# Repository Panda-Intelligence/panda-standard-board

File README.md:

# Current development entry — Panda Standard (E0.2 r26 / v0.1.1)

The current product is the **Panda Standard 4.7-inch parallel E0470A01-family single-board
engineering design**, with a replaceable 2050mAh LCO battery pack (`323576`) and a
finished-device maximum thickness of 7mm, including positive tolerances.
The exact pack identity, complete panel suffix/assembly and finished tolerance
stack remain unaccepted. A CAD candidate is **NOT FOR FABRICATION OR POWER**.

Start with [the current Single Unified PCB handoff](hardware/pico47/E02-R25-SINGLE-UNIFIED-PCB-20261029.md)
and [the Panda Standard source/build guide](hardware/pico47/README.md). Source code is
under `hardware/pico47/`; each finished single-board release (`Single.kicad_pcb` and its
native KiCad project/libraries) is committed under its version-named directory:
- [`hardware/pico47/v0.1.0/`](hardware/pico47/v0.1.0/) (`R25` full-rectangle 4-layer baseline)
- [`hardware/pico47/v0.1.1/`](hardware/pico47/v0.1.1/) (`R26` L-step 4-layer board with `X = 38.0 mm` battery bay clearance & Option 1 upper-right support bay)
Temporary generated rebuild reports and manufacturing archives remain in ignored `.work/`
or the external `panda-board-deliverables` directory.
The older Split-C1 / Product-D / Thin7 designs below are electrical donors or
historical experiments, not the current product or approval to export/order it.

Current r24 native checkpoint: **Core 16 opens; Display 0 opens; DRC errors,
warnings, parity and ERC are zero**. MUX0 is connected, while the remaining
non-ground routing is still unfinished. All 237 ground pads retain their reference
connections. **16 non-ground unconnected items remain; not for fabrication or
power.** The dated handoff records actual source replay, delivery archives and
engineering limits. Continue with
`capture_pico47_checkpoint.py --require-complete-ground`.

Run source regressions without EDA or manufacturing side effects:

```sh
python3 -m unittest discover -s hardware/pico47 -p 'test_*.py'
python3 -m unittest discover -s hardware/thin18-compact -p 'test_*.py'
```

Capture a continuation with `hardware/pico47/capture_pico47_checkpoint.py` only
after native review. It checks fresh DRC/ERC, exact rules/geometry/library
bindings and every previous native pad group. Missing evidence, lost connections
or increased opens/warnings reject the checkpoint. It never grants fabrication
or physical qualification, including when native counts happen to reach zero.

---

# Panda Standard Board

Open hardware design sources and engineering documentation for the **Panda Standard Board**, maintained by Panda Intelligence.

## Historical Split-C1 electrical donor

The historical electrical donor is the populated **Core-C1 96 x 68 mm / 4-layer** plus
**Display-C1 45 x 36 mm / 2-layer** design already split and routed on main.
Start with [Split-C1 handoff](hardware/thin18-compact/SPLIT-C1-HANDOFF.md) and the
[PG/PSEL functional migration](hardware/thin18-compact/SPLIT-C1-POWER-INTEGRITY.md).
Do not replace it with Thin7/portrait-R2 experimental CAD merely because an
experiment has a newer timestamp. Thin7 remains a separate, incomplete 7-mm
mechanical target and is not claimed by the Split-C1 bench prototype.

Inspect the historical pipeline without generating manufacturing data:

```sh
python3 hardware/thin18-compact/release_split_c1.py --target split-c1 --plan
```

Bare-board CAM/DFM, accepted PCBA supply and physical EVT are separate gates.
The new supervisor is a mainland part, but its exact assembly code/receipt is
not yet confirmed. No production qualification or actual purchase is implied.

## Historical published Thin18 baseline

The earlier published integrated-board engineering baseline was:

- **Board:** Thin18 domestic EVT
- **PCB checkpoint:** `routing142`
- **PCB SHA-256:** `ccc19c5402f633638ed72e7c94a92375684037a1f9c04f63072dc58f86c16071`
- **KiCad validation:** 0 DRC violations, 0 unconnected items, 0 schematic-parity errors; ERC 0
- **Status:** engineering / EVT — **not a manufacturing release**

The baseline includes the current right-side microSD access geometry. Manufacturing, assembly, SI/PI, RF, thermal, tolerance-stack and physical EVT qualification remain separate release gates.

## Repository layout

```text
hardware/
  thin18/
    routing142/        Current KiCad engineering baseline and machine-readable verification evidence
docs/
  design/              Electrical architecture, interfaces, power tree, constraints and design rules
  verification/        ERC/layout/fabrication-readiness engineering reviews
  mechanical/          Board/mechanical interface review notes
LICENSES/
```

## Opening the historical donor design

The design was validated with **KiCad 10.0.5**. Open the complete project under:

```text
hardware/thin18-compact/core-c1-96x68-split/eda/core/PANDA-STD-CORE-EVT/PANDA-THIN16/
hardware/thin18-compact/display-c1-45x36-production-bom/
```

Project-local symbol and footprint libraries are included where the design depends on them.

## Product visualization

Explore the [interactive Thin18 routing142 assembly model](hardware/thin18/routing142/visualization/Panda-thin18-routing142-exploded.html) or watch the [exploded-view video on YouTube](https://youtu.be/T_Nb8tvqas8).

The model is an engineering visualization for design communication. Mechanical fit and manufacturing readiness require separate validation.

## Verification boundary

A clean KiCad DRC/ERC result means the design database is internally consistent. It does **not** establish production qualification, regulatory compliance, component derating, RF performance, thermal margin, assembly yield or mechanical fit of real production parts.

Use tagged manufacturing releases, when available, for fabrication rather than assuming the newest engineering checkpoint is production-ready.

## Licensing

Hardware design sources: **CERN-OHL-S-2.0**.

Documentation: **CC BY-SA 4.0**, unless otherwise noted.

Third-party component models, symbols, footprints, manufacturer names and trademarks retain their respective rights and licensing terms.

## Split-C1 executable control follow-up

[Portable bench-control core](firmware/split_c1/README.md) implements tested
XL9535/SGM41513/SGM37601 sequencing and a read-only QMI8658A identity probe.
Host tests and native pin/address binding checks run in the explicit Split-C1
export pipeline. This is not product-firmware integration or physical EVT.
The [hardware-finish ECO](hardware/thin18-compact/SPLIT-C1-HARDWARE-FINISH.md) adds default-off charge authorization and a native GPIO2 shutdown path.
Read the updated control binding before using any older firmware. Physical EVT and accepted assembly supply remain separate gates.

## Current fabrication entry

The combined review package contains a generated `START-HERE.md`; use its
separate Core/Display Gerber paths and source hashes. The
[fabrication handoff](hardware/thin18-compact/JLC-PROTOTYPE-HANDOFF.md) now matches
the native four-layer35um Core copper construction and ENIG/green-mask selection.
C301 now has checked1.9mm round PTHs instead of short slots; the actual stackup
and assembly process still need CAM acceptance.
Native DRC/DFM success is not automatic fabrication/PCBA order approval.

## Split-C1 SMT process selection

The native [assembly-process auditor](hardware/thin18-compact/audit_split_c1_assembly_process.py)
and its tests now run before fabrication export. Core contains13 drilled vias
intersecting SMT copper lands; its order must explicitly include epoxy filling
and copper capping for the generated list. This is distinct from soldermask
tenting/plugging and must not fill component lead holes or slots. The generated
prototype package includes ASSEMBLY-PROCESS.md and per-board VIA-IN-PAD.csv,
bound to the saved PCB and checked against Excellon drill hits. Small WLCSP and
connector lands retain ENIG and need assembler stencil/process confirmation.
No source copper is changed by this audit; supplier acceptance is still required.

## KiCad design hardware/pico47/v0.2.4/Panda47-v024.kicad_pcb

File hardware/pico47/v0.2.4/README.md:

# Panda Standard 4.7 — main board v0.2.4 / E07

- **Board**: `Panda47-v024.kicad_pcb`. 4 layers, 0.8 mm. 63 × 48 mm with R4 bottom corners, the mid-mount USB-C notch
  and a speaker notch in the top-left corner, for a 67.0 × 133.7 × 7.3 mm device. See the
  [E07 note](../E07-V024-HAND-LAYOUT-SPEAKER-NOTCH-20261113.md).
- **Changes from v0.2.2**:
  - Charger, 3.3 V buck, front-light boost, RF, crystal and the VBUS / battery trunks are laid by hand
    (`../v024/design_v024.py`) and locked before autorouting. Power and HV tracks are widened after routing.
  - Cell protection moved into the pack: U907, R940, C940 and J301 are removed. J302 is a 3-pin header
    (B+ / B− / NTC) for a 3.0 × 57 × 79 mm pack with PCM and NTC.
  - Speaker notch; the audio amplifier and the speaker landing sit next to it.
  - New C817 (4.7 µF, same part as C804): VN reservoir right at the rectifier D802. New C818 (2.2 µF 0402, same
    part as C304): input capacitor at U810 pin 24. C816 dropped. C506 moved to the audio amplifier.
  - Test pads TP5 (FL_VOUT), TP6 (3V3_SD) and TPG2 (GND) added: 18 in total.
  - Connectors: the pack plugs into J302 (JST ACH 3-pin) and the antenna into J507 (MHF4); FL_PWM moved off the
    boot-strap pin (E07 note §8–9).
  - Board fixing: two soldered M1.6 nuts H2 / H3 at the top edge for screws from the back of the shell, two shell
    lips over the bottom edge, and two non-plated locating holes MH1 / MH2 for shell pins (E07 note §7 and §10).
  - Three fiducials. Net classes Power 0.3 mm, HV 0.2 mm, RF 0.17 mm.
- **Schematic**: `Panda47-v024.kicad_sch` (index) + 8 sheets, generated from the netlist. The netlist is identical to
  the board.
- **Libraries**: `Panda47v2.pretty` (the v0.2.2 set; the U901 pin-1 dot is moved). Symbols: `Panda7.kicad_sym`.
- **Native checks** (KiCad 10.0.7, in this directory): ERC 0. DRC 0 violations, 0 unconnected, 0 schematic parity
  (`--severity-all`).
- **Status**: `manufacturing_release = false`. Open items are listed in §6 of the E07 note; the main ones are a
  custom-pack quote for the cell (no datasheet exists for this size) and a speaker sample. 22 via-in-pad holes need
  resin fill and a plated cap. The order pack (153 placements, 72 BOM lines) is outside Git.

## Build path

Scripts are in `../v020/`, `../v023/` and `../v024/`; run them with `PANDA47_VARIANT=v024` and
`PANDA47_FP_DIR=hardware/pico47/v0.2.4/Panda47v2.pretty`. Freerouting is not deterministic, so this KiCad project,
not a replay, is the source of truth.

1. `make_netlist_v020.py` → netlist (174 parts including 18 test pads).
2. `v024/design_v024.py` (hand blocks → `hand.json`), `v024/make_anchors_v024.py`, `v020/place_v020.py`; run the
   three twice so the hand-copper keep-outs reach the placer. Result: `v024/layout/placement_v024.json`.
3. `build_v020_pcb.py`, `v023/precopper_v023.py` (locked hand copper), `gnd_stitch_v020.py`, Freerouting 60 passes.
4. Grid router (`router_v020.py` + `apply_router_v020.py`) with `v024/layout/spec_left.json`,
   `spec_touch_int.json` and `spec_d11.json`, with `eco_touch_int.py` and `eco_d11.py` in between (E07 note §4).
5. `finish_v020.py`, `prune_dangling_v020.py` / `trim_dangling_v020.py`, `v023/widen_v023.py`,
   `v023/fiducials_v023.py`, `silk_v020.py`, `info_silk_v02x.py` with `v024/v024_silk.json`, then
   `v024/layout/eco_final.py`.
6. `v024/layout/eco_vp.py`, `eco_pmic.py` (adds C817), the grid router with `spec_pmic.json`, prune / trim, widen
   and `silk_v020.py` again (E07 note §4 steps 9–10). The ECO scripts use `layout/ecolib.py`.
   Then `eco_cin.py` (C818, L802, C506) with `spec_cin.json`, `eco_tp.py` and `eco_tp_silk.py` (steps 11–12).
7. `build_v020_sch.py`, `sync_board_sch_v020.py`, `set_fields_v020.py`; `export_orderpack_v020.py` for the order pack.

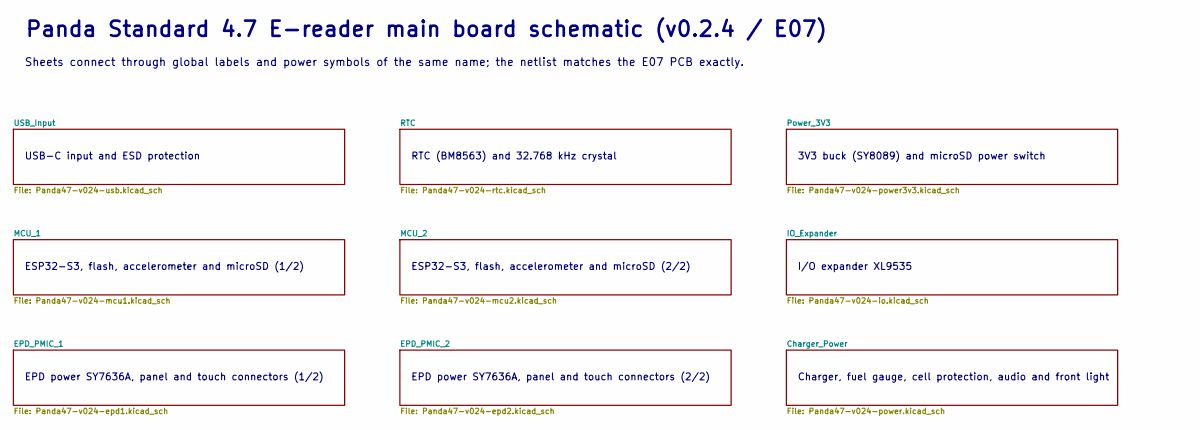
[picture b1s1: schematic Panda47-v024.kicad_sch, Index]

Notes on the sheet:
Panda Standard 4.7 E-reader main board schematic (v0.2.4 / E07)
Sheets connect through global labels and power symbols of the same name; the netlist matches the E07 PCB exactly.
USB-C input and ESD protection
RTC (BM8563) and 32.768 kHz crystal
3V3 buck (SY8089) and microSD power switch
ESP32-S3, flash, accelerometer and microSD (1/2)
ESP32-S3, flash, accelerometer and microSD (2/2)
I/O expander XL9535
EPD power SY7636A, panel and touch connectors (1/2)
EPD power SY7636A, panel and touch connectors (2/2)
Charger, fuel gauge, cell protection, audio and front light

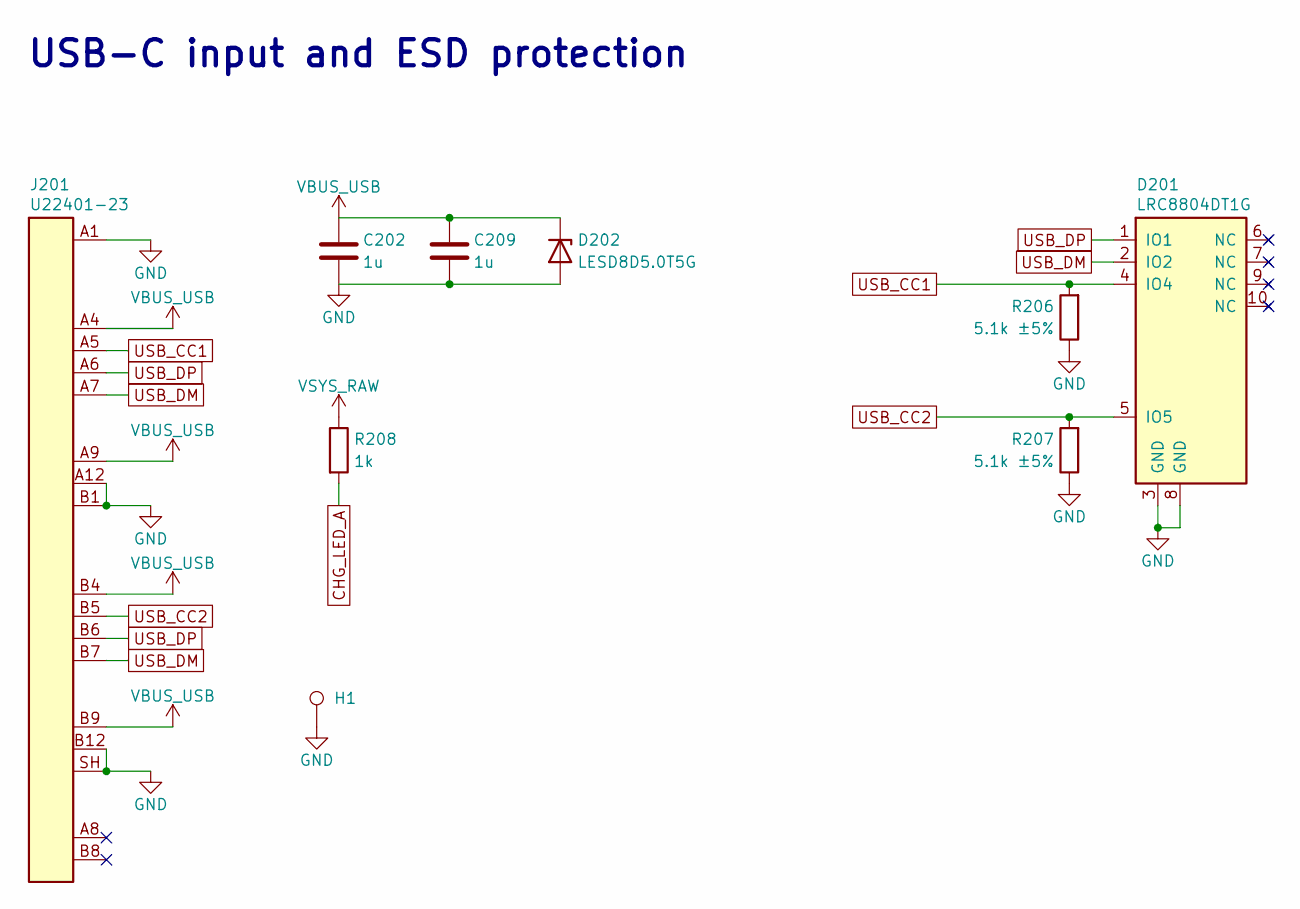
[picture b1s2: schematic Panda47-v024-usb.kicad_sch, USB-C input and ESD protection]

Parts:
C202: 1u / VBUS; C202_Core; MPN CL10A105KB8NNNC; LCSC C15849
C209: 1u; C209_Core; MPN CL10A105KB8NNNC; LCSC C15849
D201: LRC8804DT1G; D201_Core; MPN LRC8804DT1G; LCSC C2912064
D202: LESD8D5.0T5G; D202_Core; MPN LESD8D5.0T5G; LCSC C172414
H1: M1.6 SMT nut; SMTSO_M1.6_L1; MPN SMTSO1610MTJ; LCSC C2928167
J201: U22401-23 / MID-MOUNT; J201_Core; MPN U22401-23; LCSC C49325733
R206: 5.1k ±5% / USB-C Rd; R206_Core; MPN 0402WGF5101TCE; LCSC C25905
R207: 5.1k ±5% / USB-C Rd; R207_Core; MPN 0402WGF5101TCE; LCSC C25905
R208: 1k; R_0402_1005Metric; MPN 0402WGF1001TCE; LCSC C11702

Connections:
CHG_LED_A: R208.2; also elsewhere on the board
GND: C202.2, C209.2, D201.3 (GND), D201.8 (GND), D202.2 (A), H1.1, J201.A1 (A1_A1), J201.A12 (A12_A12), J201.B1 (B1_B1), J201.B12 (B12_B12), J201.SH (SH_SH), R206.1, R207.1; also elsewhere on the board
USB_CC1: D201.4 (IO4), J201.A5 (A5_A5), R206.2
USB_CC2: D201.5 (IO5), J201.B5 (B5_B5), R207.2
USB_DM: D201.2 (IO2), J201.A7 (A7_A7), J201.B7 (B7_B7); also elsewhere on the board
USB_DP: D201.1 (IO1), J201.A6 (A6_A6), J201.B6 (B6_B6); also elsewhere on the board
VBUS_USB: C202.1, C209.1, D202.1 (K), J201.A4 (A4_A4), J201.A9 (A9_A9), J201.B4 (B4_B4), J201.B9 (B9_B9); also elsewhere on the board
VSYS_RAW: R208.1; also elsewhere on the board

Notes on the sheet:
USB-C input and ESD protection

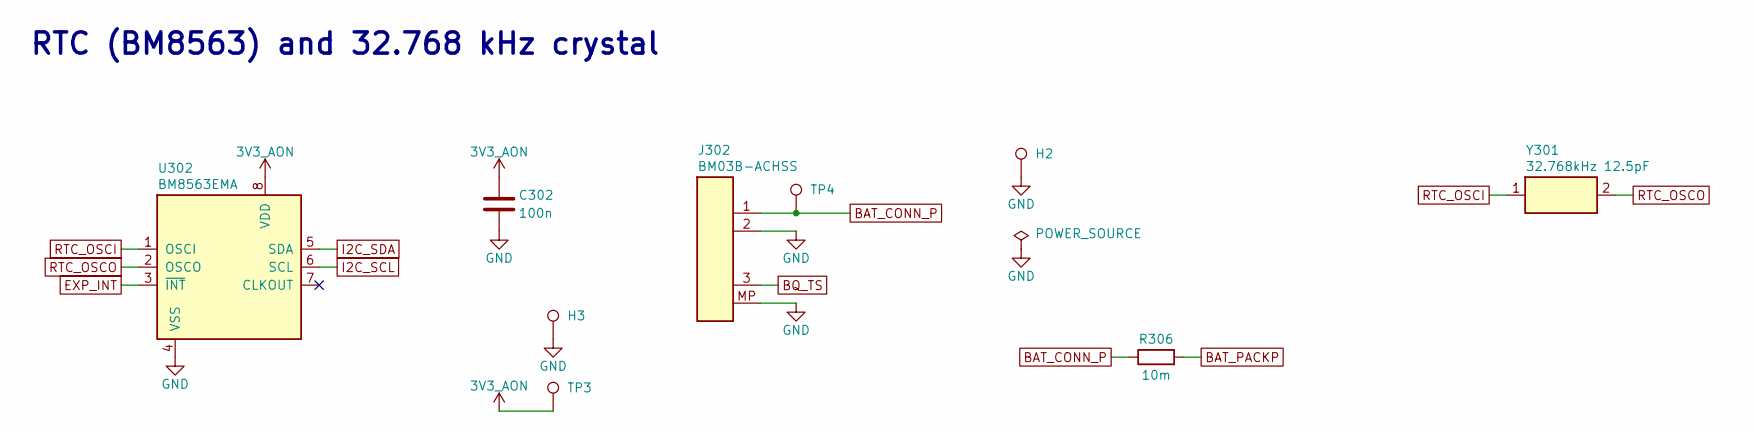
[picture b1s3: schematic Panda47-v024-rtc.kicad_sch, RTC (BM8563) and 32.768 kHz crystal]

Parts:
C302: 100n / RTC VDD; C302_Core; MPN CL05B104KB54PNC; LCSC C307331
H2, H3: M1.6 SMT nut; SMTSO_M1.6_L1; MPN SMTSO1620MTJ; LCSC C2916317
J302: BM03B-ACHSS / pack; JST_ACH_BM03B-ACHSS-GAN-ETF_1x03-1MP_P1.20mm_Vertical; MPN BM03B-ACHSS-GAN-ETF(LF)(SN); LCSC C5118705
R306: 10m / CW2217 SHUNT; R306_Core; MPN FRM121WFR010TM; LCSC C7467248
TP3: 3V3_AON; TP3_Core; MPN NOT_A_PURCHASED_PART
TP4: BAT+; TP4_Core; MPN NOT_A_PURCHASED_PART
U302: BM8563EMA; MSOP-8_3x3mm_P0.65mm; MPN BM8563EMA; LCSC C269878
Y301: 32.768kHz 12.5pF; Crystal_SMD_3215-2Pin_3.2x1.5mm; MPN X321532768KGD2SI; LCSC C620155

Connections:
3V3_AON: C302.1, TP3.1, U302.8 (VDD); also elsewhere on the board
BAT_CONN_P: J302.1, R306.1, TP4.1; also elsewhere on the board
BAT_PACKP: R306.2; also elsewhere on the board
BQ_TS: J302.3; also elsewhere on the board
EXP_INT: U302.3 (~INT); also elsewhere on the board
GND: C302.2, H2.1, H3.1, J302.2, J302.MP, U302.4 (VSS); also elsewhere on the board
I2C_SCL: U302.6 (SCL); also elsewhere on the board
I2C_SDA: U302.5 (SDA); also elsewhere on the board
RTC_OSCI: U302.1 (OSCI), Y301.1
RTC_OSCO: U302.2 (OSCO), Y301.2

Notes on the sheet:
RTC (BM8563) and 32.768 kHz crystal

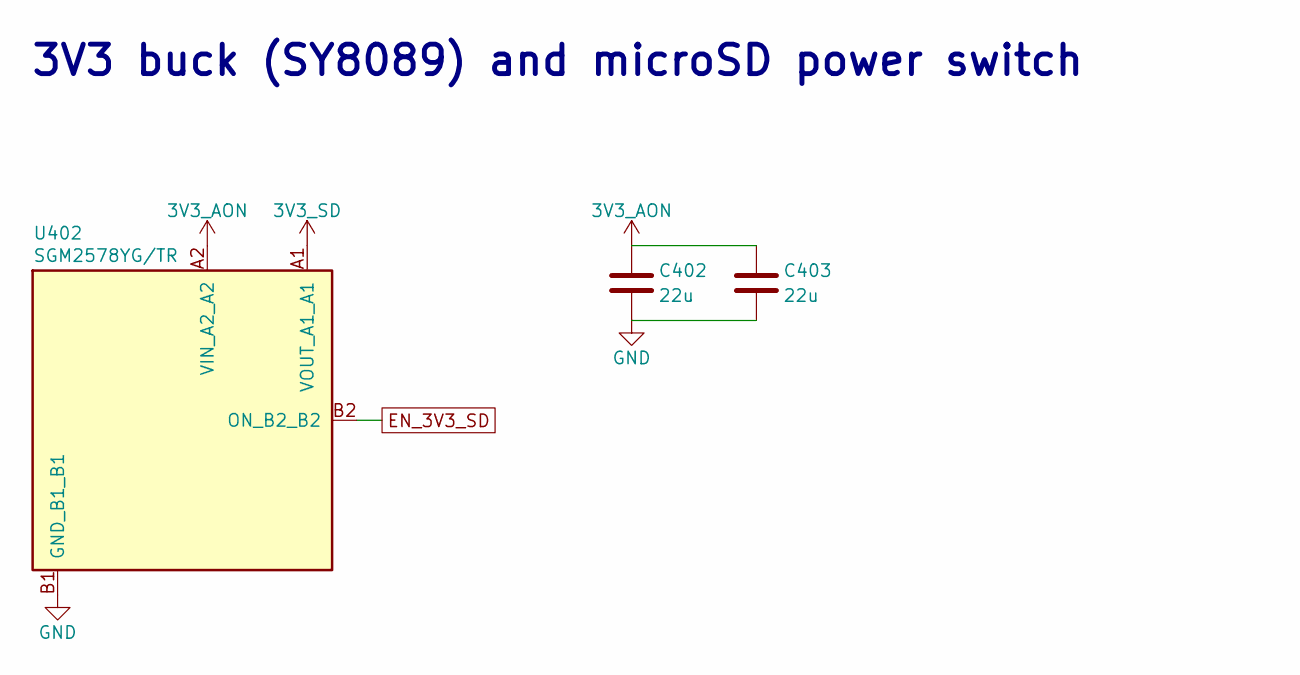
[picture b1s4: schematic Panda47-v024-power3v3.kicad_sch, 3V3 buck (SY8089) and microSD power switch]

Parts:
C402: 22u / VOUT; C402_Core; MPN TCC0603X5R226M100CT; LCSC C20416425
C403: 22u / VOUT; C403_Core; MPN TCC0603X5R226M100CT; LCSC C20416425
U402: SGM2578YG/TR; U402_Core; MPN SGM2578YG/TR; LCSC C403706

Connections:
3V3_AON: C402.1, C403.1, U402.A2 (VIN_A2_A2); also elsewhere on the board
3V3_SD: U402.A1 (VOUT_A1_A1); also elsewhere on the board
EN_3V3_SD: U402.B2 (ON_B2_B2); also elsewhere on the board
GND: C402.2, C403.2, U402.B1 (GND_B1_B1); also elsewhere on the board

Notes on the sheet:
3V3 buck (SY8089) and microSD power switch

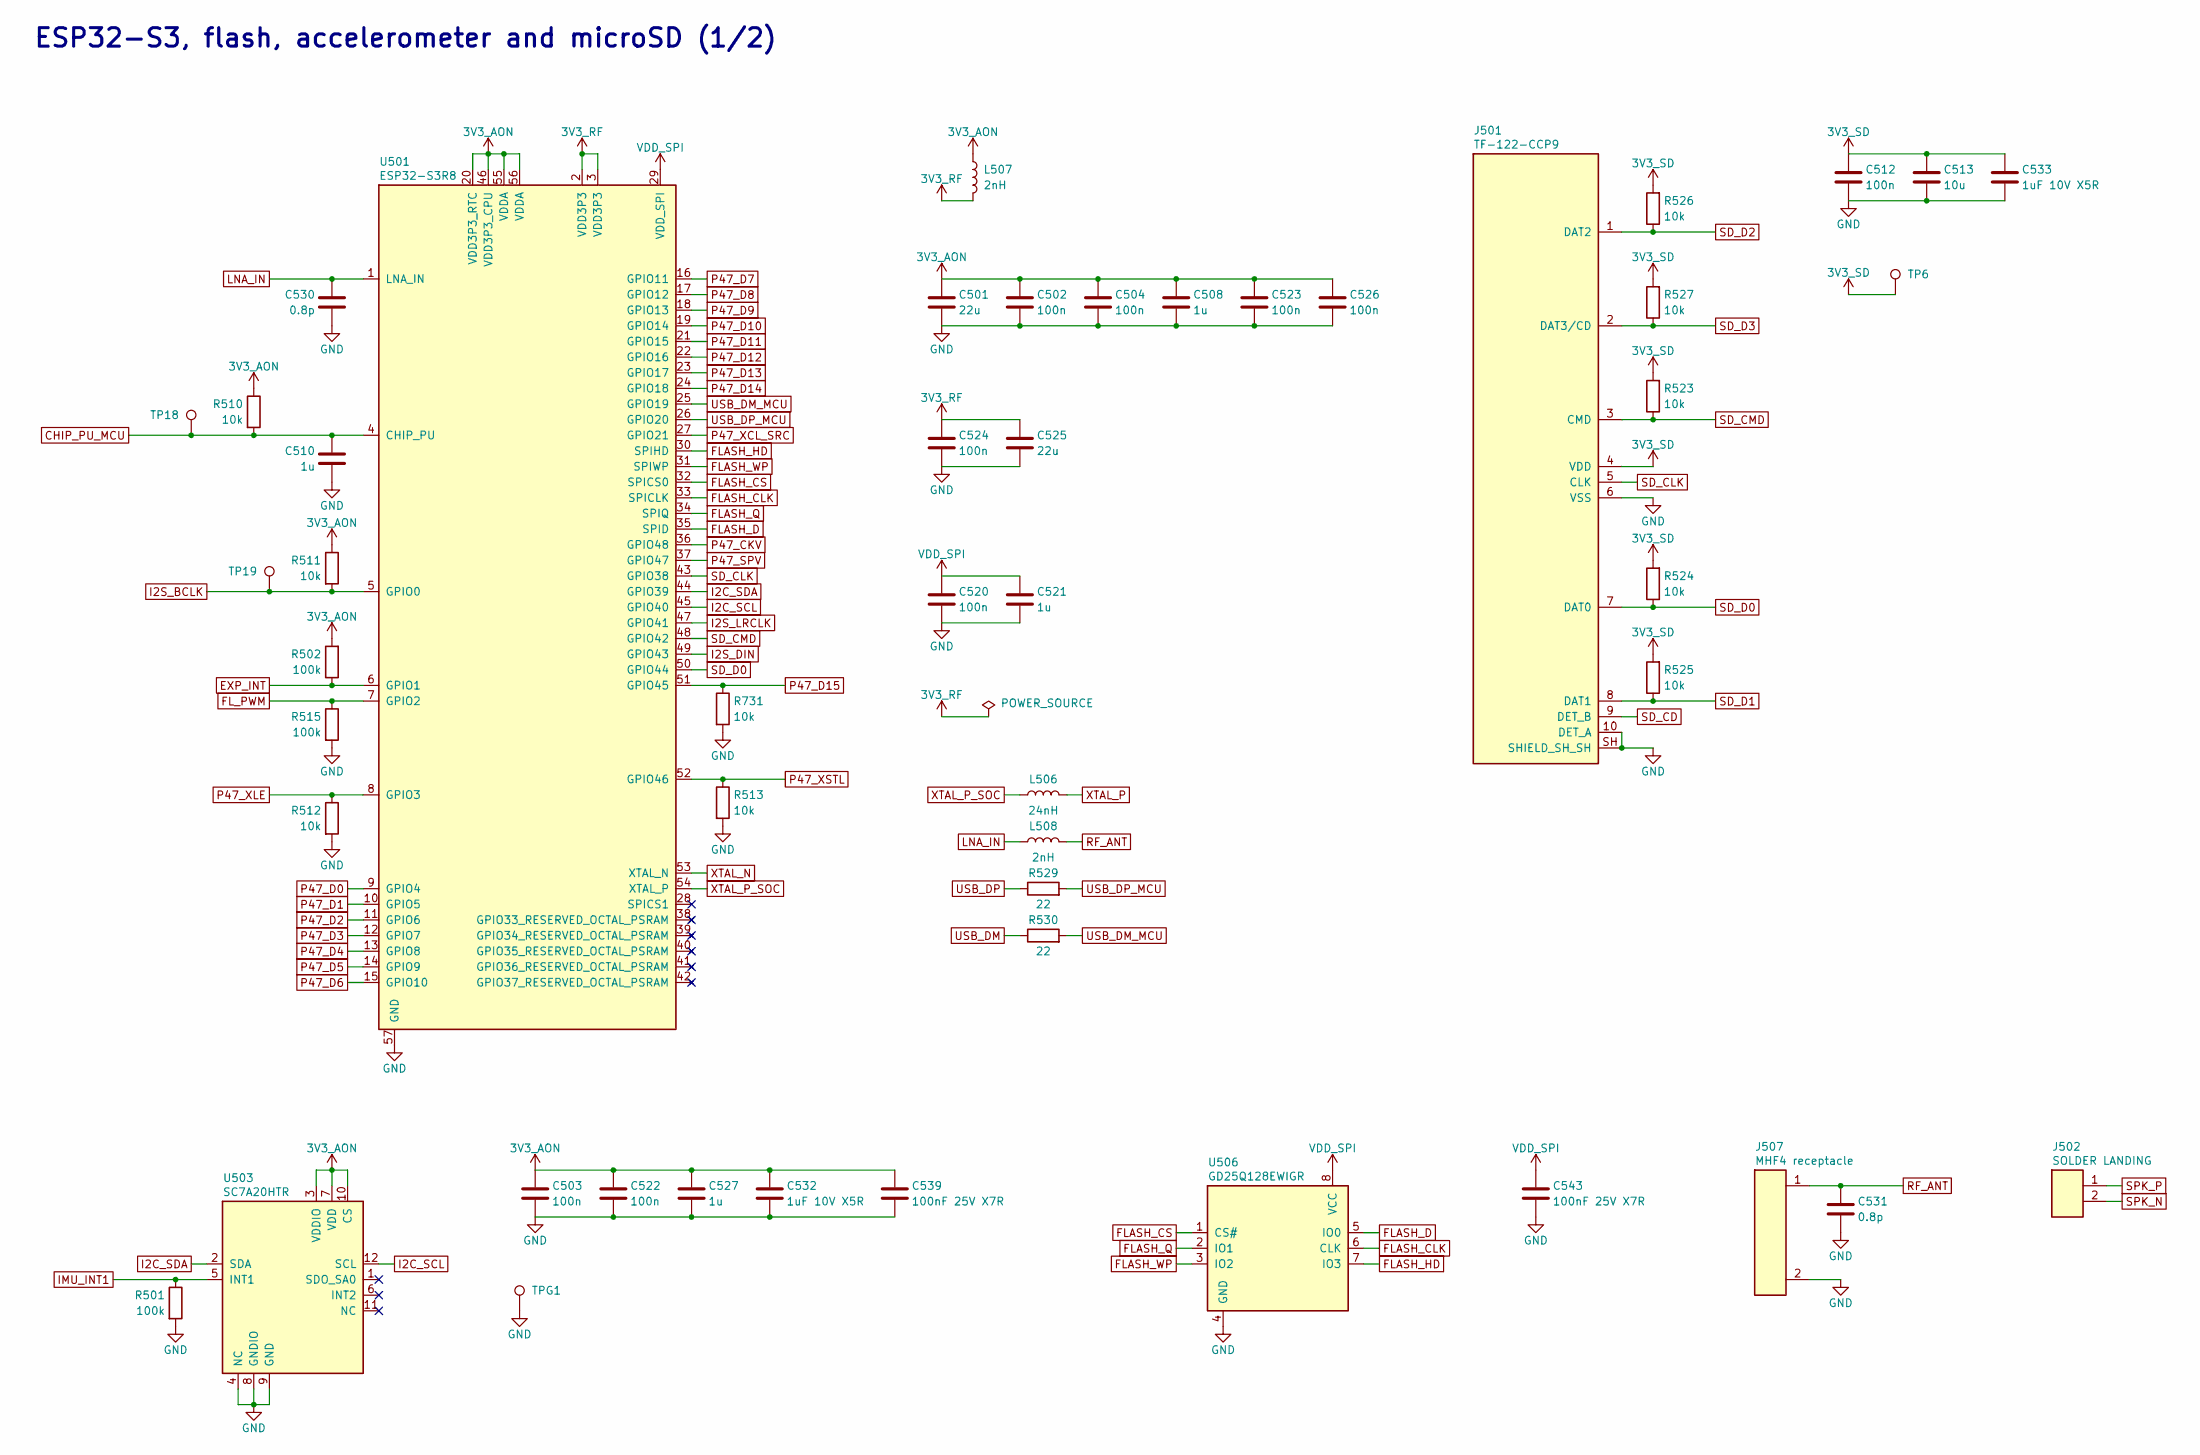
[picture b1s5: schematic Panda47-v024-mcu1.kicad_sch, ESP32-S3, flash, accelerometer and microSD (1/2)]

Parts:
C501: 22u / ESP32; C501_Core; MPN TCC0603X5R226M100CT; LCSC C20416425
C502: 100n / ESP32; C502_Core; MPN CL05B104KB54PNC; LCSC C307331
C503: 100n / VDD_IO; C503_Core; MPN CL05B104KB54PNC; LCSC C307331
C504: 100n / VDD; C504_Core; MPN CL05B104KB54PNC; LCSC C307331
C508: 1u / U402 VIN; C508_Core; MPN CL10A105KB8NNNC; LCSC C15849
C510: 1u / CHIP_PU; C510_Core; MPN CL10A105KB8NNNC; LCSC C15849
C512: 100n / SD VDD; C512_Core; MPN CL05B104KB54PNC; LCSC C307331
C513: 10u / SD VDD; C513_Core; MPN CL10A106MA8NRNC; LCSC C96446
C520: 100n; C520_Core; MPN CL05B104KB54PNC; LCSC C307331
C521: 1u; C521_Core; MPN CL05A105KA5NQNC; LCSC C52923
C522: 100n; C522_Core; MPN CL05B104KB54PNC; LCSC C307331
C523: 100n; C523_Core; MPN CL05B104KB54PNC; LCSC C307331
C524: 100n; C524_Core; MPN CL05B104KB54PNC; LCSC C307331
C525: 22u / local RF supply; C525_Core; MPN CL21A226MAQNNNE; LCSC C45783
C526: 100n; C526_Core; MPN CL05B104KB54PNC; LCSC C307331
C527: 1u; C527_Core; MPN CL05A105KA5NQNC; LCSC C52923
C530: 0.8p / RF; C530_Core; MPN 0402CG0R8C500NT; LCSC C40459
C531: 0.8p / RF; C531_Core; MPN 0402CG0R8C500NT; LCSC C40459
C532: 1uF 10V X5R / U404 COUT; C532_Core; MPN CL05A105KA5NQNC; LCSC C52923
C533: 1uF 10V X5R / U402 COUT; C533_Core; MPN CL05A105KA5NQNC; LCSC C52923
C539: 100nF 25V X7R / U503 VDD_IO; C539_Core; MPN CL05B104KB54PNC; LCSC C307331
C543: 100nF 25V X7R / U506 VCC; C543_Core; MPN CL05B104KB54PNC; LCSC C307331
J501: TF-122-CCP9 / microSD; J501_Core; MPN TF-122-CCP9; LCSC C41347844
J502: SOLDER LANDING / J502; J502_Core; MPN NOT_A_PURCHASED_PART
J507: MHF4 receptacle; MHF4_KH-IPEX4-2020; MPN KH-IPEX4-2020; LCSC C530666
L506: 24nH / crystal; L506_Core; MPN SDCL1005C24NJTDF; LCSC C74301
L507: 2nH / RF supply; L507_Core; MPN SDCL1608C2N0STDF; LCSC C370234
L508: 2nH / RF match; L508_Core; MPN SDCL1005C2N0STDF; LCSC C43365
R501: 100k / IMU_INT1; R501_Core; MPN 0402WGF1003TCE; LCSC C25741
R502: 100k / EXP_INT_PU; R502_Core; MPN 0402WGF1003TCE; LCSC C25741
R510: 10k / CHIP_PU; R510_Core; MPN 0402WGF1002TCE; LCSC C25744
R511: 10k / GPIO0; R511_Core; MPN 0402WGF1002TCE; LCSC C25744
R512: 10k / GPIO3; R512_Core; MPN 0402WGF1002TCE; LCSC C25744
R513: 10k / GPIO46; R513_Core; MPN 0402WGF1002TCE; LCSC C25744
R515: 100k / FL_PWM_PD; R_0402_1005Metric; MPN 0402WGF1003TCE; LCSC C25741
R523: 10k / SD pull-up; R523_Core; MPN 0402WGF1002TCE; LCSC C25744
R524: 10k / SD pull-up; R524_Core; MPN 0402WGF1002TCE; LCSC C25744
R525: 10k / SD pull-up; R525_Core; MPN 0402WGF1002TCE; LCSC C25744
R526: 10k / SD pull-up; R526_Core; MPN 0402WGF1002TCE; LCSC C25744
R527: 10k / SD pull-up; R527_Core; MPN 0402WGF1002TCE; LCSC C25744
R529: 22; R529_Core; MPN 0402WGF220JTCE; LCSC C25092
R530: 22; R530_Core; MPN 0402WGF220JTCE; LCSC C25092
R731: 10k; R731_Core; MPN 0402WGF1002TCE; LCSC C25744
TP6: 3V3_SD; TP801_Display; MPN NOT_A_PURCHASED_PART
TP18: CHIP_PU; TP18_Core; MPN NOT_A_PURCHASED_PART
TP19: GPIO0 / BOOT; TP18_Core
TPG1: GND; TPG1_Core; MPN NOT_A_PURCHASED_PART
U501: ESP32-S3R8; U501_Core; MPN ESP32-S3R8; LCSC C2913194
U503: SC7A20HTR; LGA-12_2x2mm_P0.5mm; MPN SC7A20HTR; LCSC C19274408
U506: GD25Q128EWIGR; WSON-8-1EP_6x5mm_P1.27mm_EP3.4x4mm; MPN GD25Q128EWIGR; LCSC C2982923

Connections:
3V3_AON: C501.1, C502.1, C503.1, C504.1, C508.1, C522.1, C523.1, C526.1, C527.1, C532.1, C539.1, L507.1, R502.2, R510.1, R511.1, U501.20 (VDD3P3_RTC), U501.46 (VDD3P3_CPU), U501.55 (VDDA), U501.56 (VDDA), U503.3 (VDDIO), U503.7 (VDD), U503.10 (CS); also elsewhere on the board
3V3_RF: C524.1, C525.1, L507.2, U501.2 (VDD3P3), U501.3 (VDD3P3)
3V3_SD: C512.1, C513.1, C533.1, J501.4 (VDD), R523.2, R524.2, R525.2, R526.2, R527.2, TP6.1; also elsewhere on the board
CHIP_PU_MCU: C510.1, R510.2, TP18.1, U501.4 (CHIP_PU)
EXP_INT: R502.1, U501.6 (GPIO1); also elsewhere on the board
FLASH_CLK: U501.33 (SPICLK), U506.6 (CLK)
FLASH_CS: U501.32 (SPICS0), U506.1 (CS#)
FLASH_D: U501.35 (SPID), U506.5 (IO0)
FLASH_HD: U501.30 (SPIHD), U506.7 (IO3)
FLASH_Q: U501.34 (SPIQ), U506.2 (IO1)
FLASH_WP: U501.31 (SPIWP), U506.3 (IO2)
FL_PWM: R515.1, U501.7 (GPIO2); also elsewhere on the board
GND: C501.2, C502.2, C503.2, C504.2, C508.2, C510.2, C512.2, C513.2, C520.2, C521.2, C522.2, C523.2, C524.2, C525.2, C526.2, C527.2, C530.2, C531.2, C532.2, C533.2, C539.2, C543.2, J501.6 (VSS), J501.10 (DET_A), J501.SH (SHIELD_SH_SH), J507.2, R501.2, R512.2, R513.2, R515.2, R731.2, TPG1.1, U501.57 (GND), U503.4 (NC), U503.8 (GNDIO), U503.9 (GND), U506.4 (GND); also elsewhere on the board
I2C_SCL: U501.45 (GPIO40), U503.12 (SCL); also elsewhere on the board
I2C_SDA: U501.44 (GPIO39), U503.2 (SDA); also elsewhere on the board
I2S_BCLK: R511.2, TP19.1, U501.5 (GPIO0); also elsewhere on the board
I2S_DIN: U501.49 (GPIO43); also elsewhere on the board
I2S_LRCLK: U501.47 (GPIO41); also elsewhere on the board
IMU_INT1: R501.1, U503.5 (INT1); also elsewhere on the board
LNA_IN: C530.1, L508.1, U501.1 (LNA_IN)
P47_CKV: U501.36 (GPIO48); also elsewhere on the board
P47_D0: U501.9 (GPIO4); also elsewhere on the board
P47_D1: U501.10 (GPIO5); also elsewhere on the board
P47_D2: U501.11 (GPIO6); also elsewhere on the board
P47_D3: U501.12 (GPIO7); also elsewhere on the board
P47_D4: U501.13 (GPIO8); also elsewhere on the board
P47_D5: U501.14 (GPIO9); also elsewhere on the board
P47_D6: U501.15 (GPIO10); also elsewhere on the board
P47_D7: U501.16 (GPIO11); also elsewhere on the board
P47_D8: U501.17 (GPIO12); also elsewhere on the board
P47_D9: U501.18 (GPIO13); also elsewhere on the board
P47_D10: U501.19 (GPIO14); also elsewhere on the board
P47_D11: U501.21 (GPIO15); also elsewhere on the board
P47_D12: U501.22 (GPIO16); also elsewhere on the board
P47_D13: U501.23 (GPIO17); also elsewhere on the board
P47_D14: U501.24 (GPIO18); also elsewhere on the board
P47_D15: R731.1, U501.51 (GPIO45); also elsewhere on the board
P47_SPV: U501.37 (GPIO47); also elsewhere on the board
P47_XCL_SRC: U501.27 (GPIO21); also elsewhere on the board
P47_XLE: R512.1, U501.8 (GPIO3); also elsewhere on the board
P47_XSTL: R513.1, U501.52 (GPIO46); also elsewhere on the board
RF_ANT: C531.1, J507.1, L508.2
SD_CD: J501.9 (DET_B); also elsewhere on the board
SD_CLK: J501.5 (CLK), U501.43 (GPIO38)
SD_CMD: J501.3 (CMD), R523.1, U501.48 (GPIO42)
SD_D0: J501.7 (DAT0), R524.1, U501.50 (GPIO44)
SD_D1: J501.8 (DAT1), R525.1
SD_D2: J501.1 (DAT2), R526.1
SD_D3: J501.2 (DAT3/CD), R527.1
SPK_N: J502.2; also elsewhere on the board
SPK_P: J502.1; also elsewhere on the board
USB_DM: R530.1; also elsewhere on the board
USB_DM_MCU: R530.2, U501.25 (GPIO19)
USB_DP: R529.1; also elsewhere on the board
USB_DP_MCU: R529.2, U501.26 (GPIO20)
VDD_SPI: C520.1, C521.1, C543.1, U501.29 (VDD_SPI), U506.8 (VCC)
XTAL_N: U501.53 (XTAL_N); also elsewhere on the board
XTAL_P: L506.2; also elsewhere on the board
XTAL_P_SOC: L506.1, U501.54 (XTAL_P)

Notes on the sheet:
ESP32-S3, flash, accelerometer and microSD (1/2)

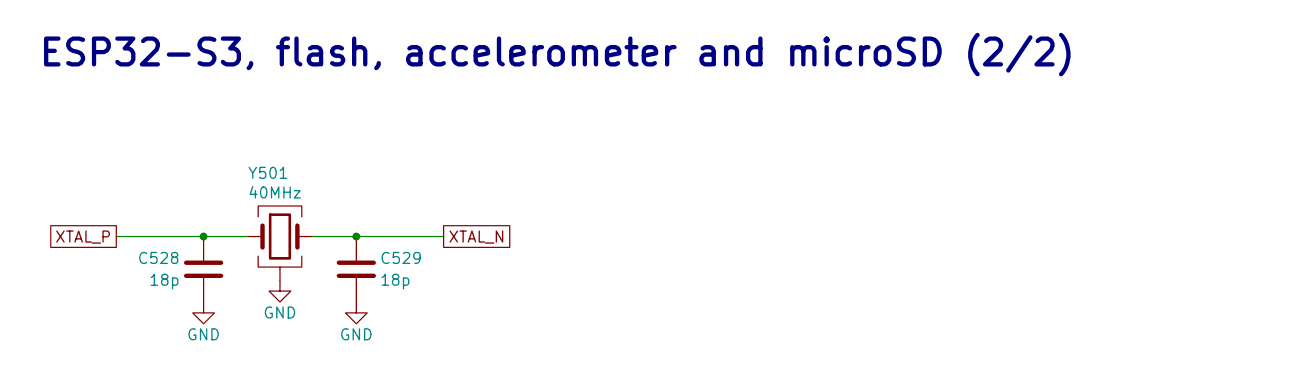
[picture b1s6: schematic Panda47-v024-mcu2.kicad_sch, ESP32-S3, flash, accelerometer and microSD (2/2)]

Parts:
C528: 18p / crystal; C528_Core; MPN 0402CG180J500NT; LCSC C1549
C529: 18p / crystal; C529_Core; MPN 0402CG180J500NT; LCSC C1549
Y501: 40MHz / 12pF; Y501_Core; MPN XL2EL89COI-111YLC-40M; LCSC C18214314

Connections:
GND: C528.2, C529.2, Y501.2, Y501.4; also elsewhere on the board
XTAL_N: C529.1, Y501.3; also elsewhere on the board
XTAL_P: C528.1, Y501.1; also elsewhere on the board

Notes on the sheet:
ESP32-S3, flash, accelerometer and microSD (2/2)

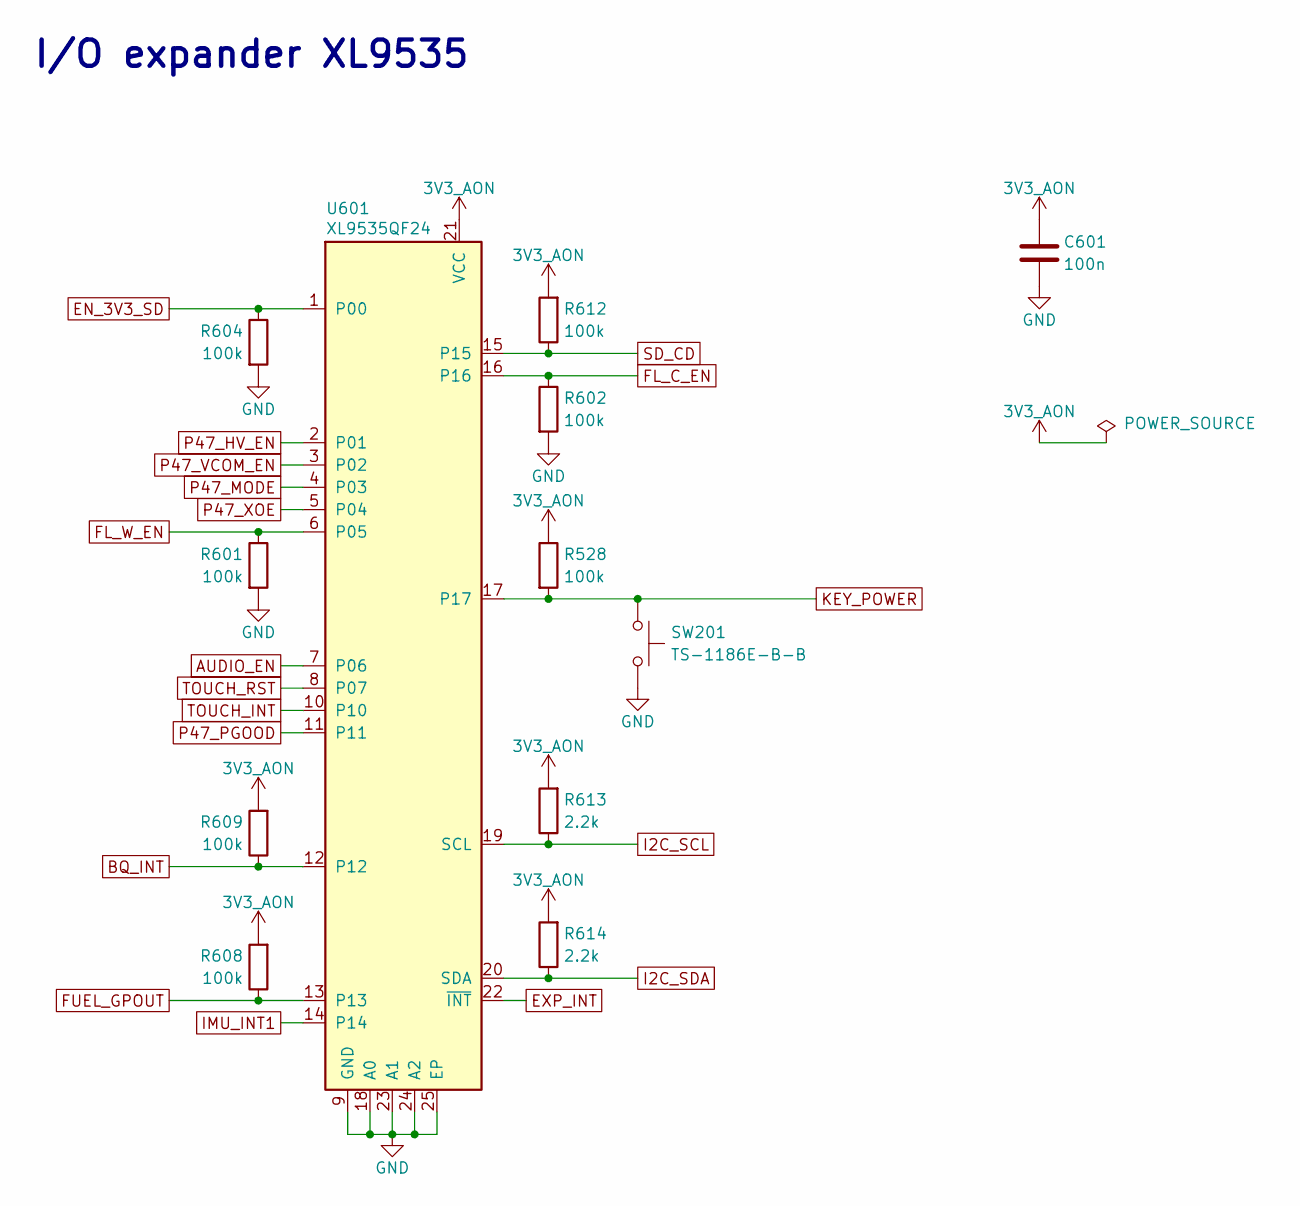
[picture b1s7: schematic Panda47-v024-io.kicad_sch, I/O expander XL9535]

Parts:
C601: 100n / U601 VCC; C601_Core; MPN CL05B104KB54PNC; LCSC C307331
R528, R602: 100k; R_0402_1005Metric; MPN 0402WGF1003TCE; LCSC C25741
R601: 100k / FL_HWEN_PD; R601_Core; MPN 0402WGF1003TCE; LCSC C25741
R604: 100k / SD_EN_PD; R604_Core; MPN 0402WGF1003TCE; LCSC C25741
R608: 100k / FUEL_PU; R608_Core; MPN 0402WGF1003TCE; LCSC C25741
R609: 100k / BQ_INT_PU; R609_Core; MPN 0402WGF1003TCE; LCSC C25741
R612: 100k / SD_CD_PU; R612_Core; MPN 0402WGF1003TCE; LCSC C25741
R613: 2.2k / I2C_SCL_PU A; R613_Core; MPN 0402WGF2201TCE; LCSC C25879
R614: 2.2k / I2C_SDA_PU A; R614_Core; MPN 0402WGF2201TCE; LCSC C25879
SW201: TS-1186E-B-B; SW201_Core; MPN TS-1186E-B-B; LCSC C2885153
U601: XL9535QF24; QFN-24-1EP_4x4mm_P0.5mm_EP2.7x2.7mm; MPN XL9535QF24; LCSC C5444301

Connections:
3V3_AON: C601.1, R528.1, R608.2, R609.2, R612.2, R613.2, R614.2, U601.21 (VCC); also elsewhere on the board
AUDIO_EN: U601.7 (P06); also elsewhere on the board
BQ_INT: R609.1, U601.12; also elsewhere on the board
EN_3V3_SD: R604.1, U601.1 (P00); also elsewhere on the board
EXP_INT: U601.22 (~INT); also elsewhere on the board
FL_C_EN: R602.1, U601.16; also elsewhere on the board
FL_W_EN: R601.1, U601.6 (P05); also elsewhere on the board
FUEL_GPOUT: R608.1, U601.13; also elsewhere on the board
GND: C601.2, R601.2, R602.2, R604.2, SW201.2, U601.9 (GND), U601.18 (A0), U601.23 (A1), U601.24 (A2), U601.25 (EP); also elsewhere on the board
I2C_SCL: R613.1, U601.19 (SCL); also elsewhere on the board
I2C_SDA: R614.1, U601.20 (SDA); also elsewhere on the board
IMU_INT1: U601.14; also elsewhere on the board
KEY_POWER: R528.2, SW201.1, U601.17
P47_HV_EN: U601.2 (P01); also elsewhere on the board
P47_MODE: U601.4 (P03); also elsewhere on the board
P47_PGOOD: U601.11; also elsewhere on the board
P47_VCOM_EN: U601.3 (P02); also elsewhere on the board
P47_XOE: U601.5 (P04); also elsewhere on the board
SD_CD: R612.1, U601.15; also elsewhere on the board
TOUCH_INT: U601.10; also elsewhere on the board
TOUCH_RST: U601.8 (P07); also elsewhere on the board

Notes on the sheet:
I/O expander XL9535
